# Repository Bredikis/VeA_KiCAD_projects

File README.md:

VeA_KiCAD_prj
 This repository is used for homeworks for KiCAD course.

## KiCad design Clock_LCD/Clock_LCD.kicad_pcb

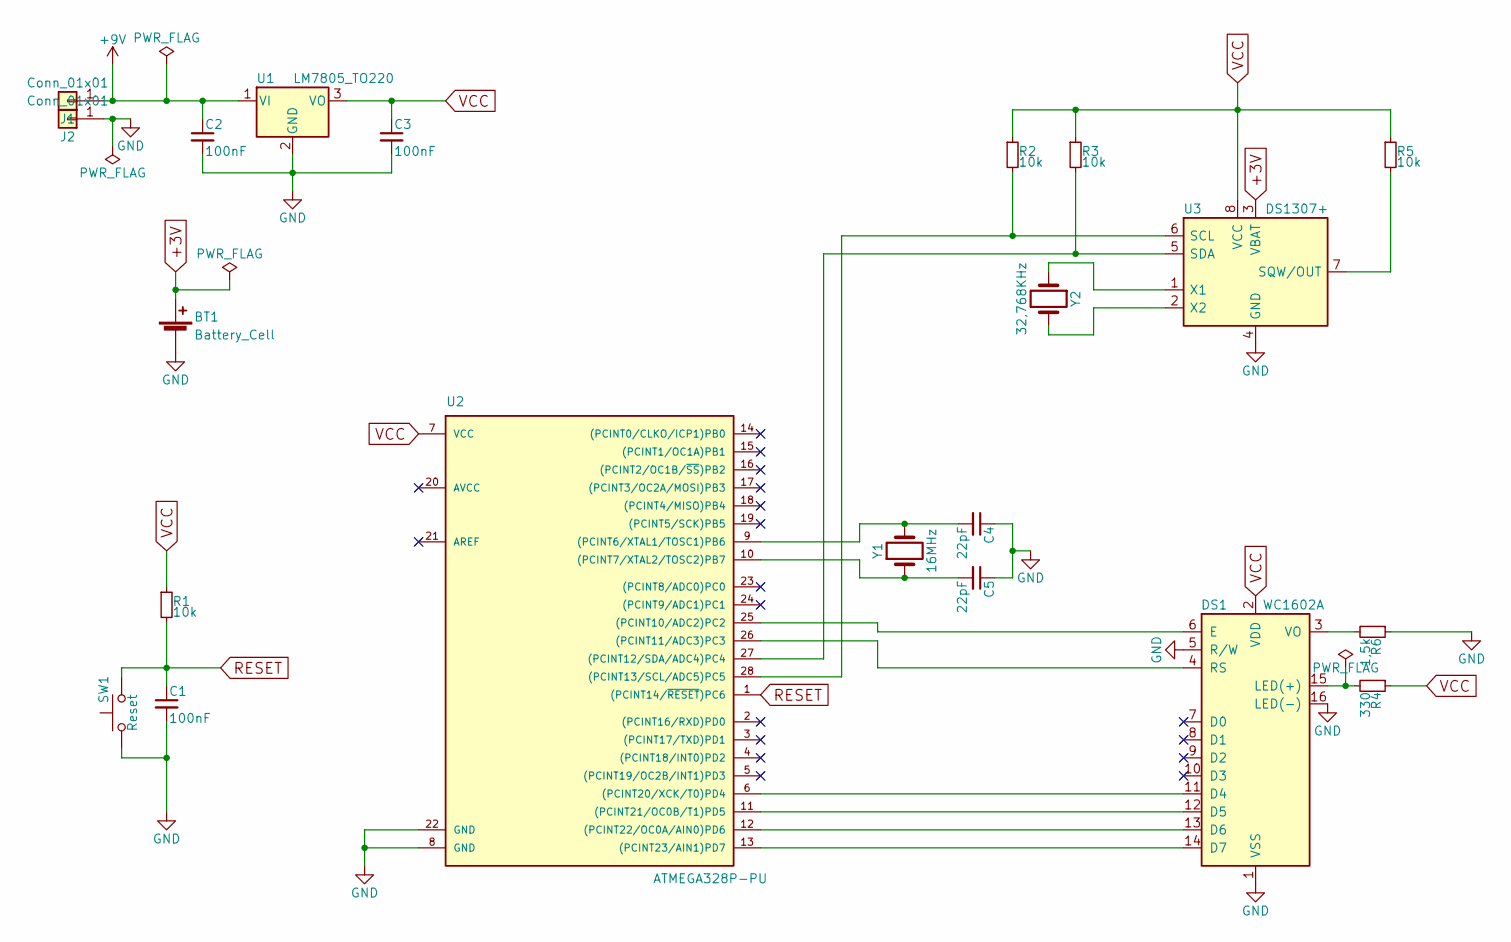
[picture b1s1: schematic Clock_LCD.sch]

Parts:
BT1: Battery_Cell; Keystone_103_1x20mm-CoinCell
C1, C2, C3: 100nF; C_0805_HandSoldering
C4, C5: 22pF; C_0805_HandSoldering
DS1: WC1602A
J1, J2: Conn_01x01; MountingHole_3.2mm_M3
R1, R2, R3, R5: 10k; R_0805_HandSoldering
R4: 330; R_0805_HandSoldering
R6: 1,5k; R_0805_HandSoldering
SW1: Reset; SW_PUSH_6mm_h5mm
U1: LM7805_TO220; TO-220-3_Vertical
U2: ATMEGA328P-PU; DIP-28_W15.24mm_Socket
U3: DS1307+; DIP-8_W7.62mm
Y1: 16MHz; Crystal_HC49-U_Vertical
Y2: 32,768KHz; Crystal_C26-LF_d2.1mm_l6.5mm_Horizontal

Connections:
+3V: BT1.1 (+), U3.3 (VBAT)
+9V: C2.1, J1.1, U1.1 (VI)
GND: BT1.2 (-), C1.2, C2.2, C3.2, C4.1, C5.1, DS1.1 (VSS), DS1.5 (R/W), DS1.16 (LED(-)), J2.1, R6.1, SW1.1, U1.2 (GND), U2.8 (GND), U2.22 (GND), U3.4 (GND)
unnamed: C4.2, U2.9 ((PCINT6/XTAL1/TOSC1)PB6), Y1.2
unnamed: C5.2, U2.10 ((PCINT7/XTAL2/TOSC2)PB7), Y1.1
unnamed: DS1.3 (VO), R6.2
unnamed: DS1.4 (RS), U2.26 ((PCINT11/ADC3)PC3)
unnamed: DS1.6 (E), U2.25 ((PCINT10/ADC2)PC2)
unnamed: DS1.11 (D4), U2.6 ((PCINT20/XCK/T0)PD4)
unnamed: DS1.12 (D5), U2.11 ((PCINT21/OC0B/T1)PD5)
unnamed: DS1.13 (D6), U2.12 ((PCINT22/OC0A/AIN0)PD6)
unnamed: DS1.14 (D7), U2.13 ((PCINT23/AIN1)PD7)
unnamed: DS1.15 (LED(+)), R4.2
unnamed: R2.2, U2.28 ((PCINT13/SCL/ADC5)PC5), U3.6 (SCL)
unnamed: R3.2, U2.27 ((PCINT12/SDA/ADC4)PC4), U3.5 (SDA)
unnamed: R5.2, U3.7 (SQW/OUT)
unnamed: U3.1 (X1), Y2.1
unnamed: U3.2 (X2), Y2.2
RESET: C1.1, R1.2, SW1.2, U2.1 ((PCINT14/~RESET~)PC6)
VCC: C3.1, DS1.2 (VDD), R1.1, R2.1, R3.1, R4.1, R5.1, U1.3 (VO), U2.7 (VCC), U3.8 (VCC)

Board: 2 copper layers, 21 parts (0 on the bottom side), 20 nets, no tracks yet.

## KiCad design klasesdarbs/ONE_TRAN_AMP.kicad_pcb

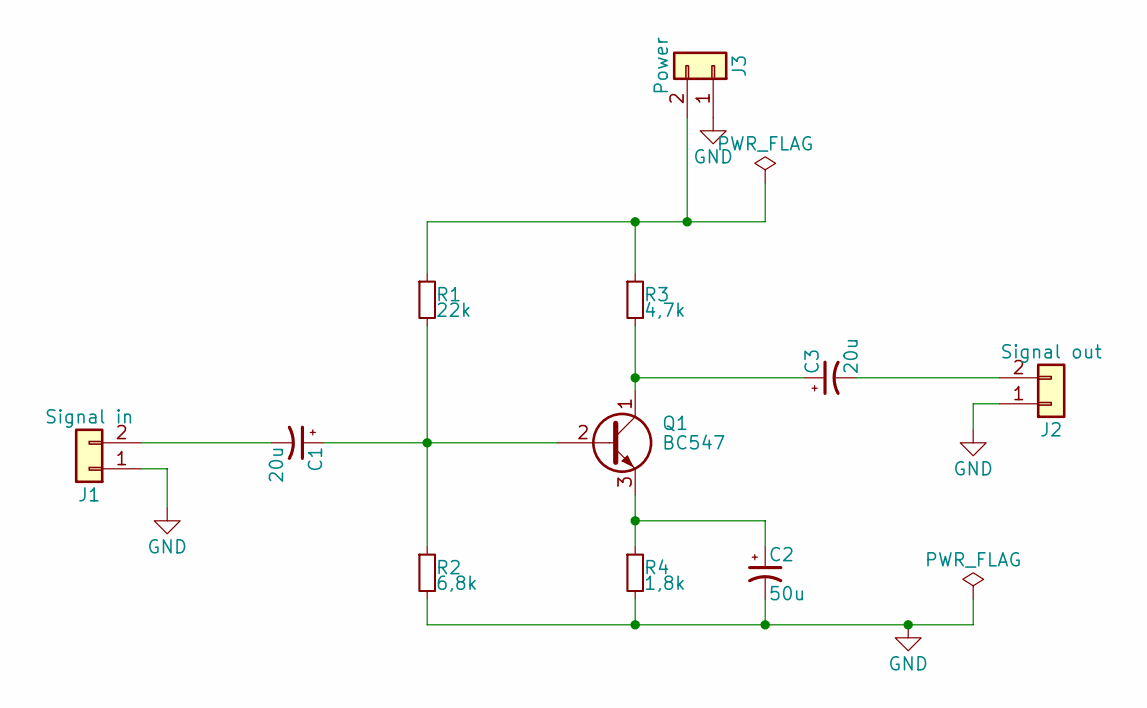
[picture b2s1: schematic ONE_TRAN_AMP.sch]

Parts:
C1, C3: 20u; CP_Radial_D10.0mm_P5.00mm
C2: 50u; CP_Radial_D10.0mm_P5.00mm
J1: Signal in; TerminalBlock_Altech_AK300-2_P5.00mm
J2: Signal out; TerminalBlock_Altech_AK300-2_P5.00mm
J3: Power; TerminalBlock_Altech_AK300-2_P5.00mm
Q1: BC547; TO-92_Molded_Narrow
R1: 22k; R_Axial_DIN0204_L3.6mm_D1.6mm_P7.62mm_Horizontal
R2: 6,8k; R_Axial_DIN0204_L3.6mm_D1.6mm_P7.62mm_Horizontal
R3: 4,7k; R_Axial_DIN0204_L3.6mm_D1.6mm_P7.62mm_Horizontal
R4: 1,8k; R_Axial_DIN0204_L3.6mm_D1.6mm_P7.62mm_Horizontal

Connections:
GND: C2.2, J1.1, J2.1, J3.1, R2.2, R4.2
unnamed: C1.1, Q1.2 (B), R1.2, R2.1
unnamed: C1.2, J1.2
unnamed: C2.1, Q1.3 (E), R4.1
unnamed: C3.1, Q1.1 (C), R3.2
unnamed: C3.2, J2.2
unnamed: J3.2, R1.1, R3.1

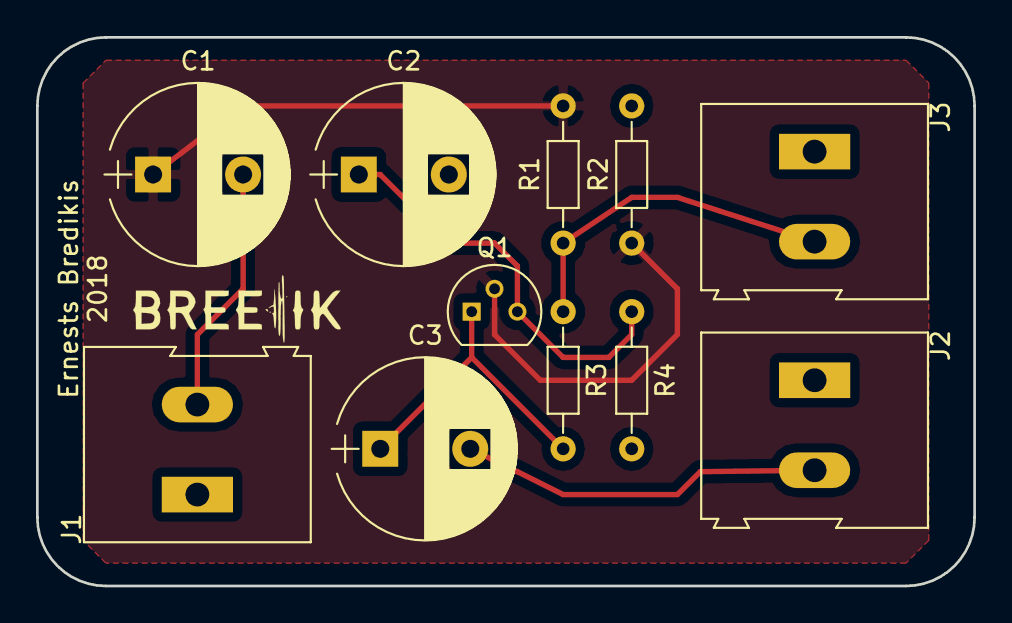
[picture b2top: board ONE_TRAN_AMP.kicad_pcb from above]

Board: 2 copper layers, 52.1 x 30.5 mm, 11 parts (0 on the bottom side), 7 nets.

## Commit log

2018-05-07 Commit all
2018-05-07 course work
2018-05-07 komponenetes vietas izmaina
